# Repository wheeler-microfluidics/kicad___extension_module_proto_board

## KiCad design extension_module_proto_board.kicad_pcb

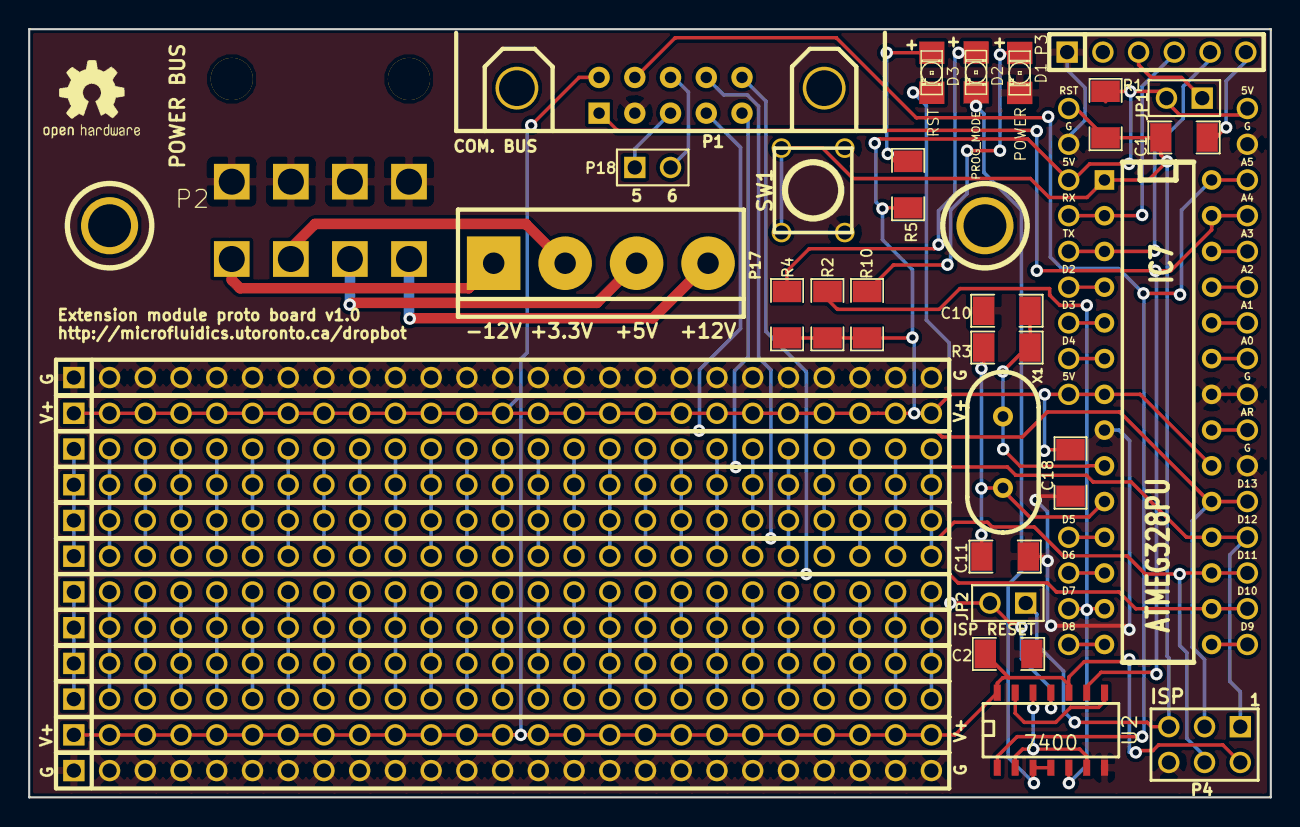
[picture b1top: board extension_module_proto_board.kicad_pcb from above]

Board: 2 copper layers, 88.3 x 54.6 mm, 41 parts (0 on the bottom side), 91 nets.

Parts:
1PIN, 1PIN#2: P***; 1pin
C1, C2, C18: 0.1uF; SM1206
C10, C11: 22pF; SM1206
D1: POWER; LED-1206
D2: PROG_MODE; LED-1206
D3: RST; LED-1206
IC7: ATMEG328PU; DIP-28
JP1: JUMPER; PIN_ARRAY_2X1
JP2: ISP RESET; PIN_ARRAY_2X1
P1: CONN_10; HE10-10C
P2: CONN_8; Molex_4x2_Mini_Fit_Jr_RA
P3: CONN_6; PIN_ARRAY-6X1
P4: CONN_6; pin_array_3x2
P5, P6, P7, P8, P9, P10, P11, P12, P13, P14, P15, P16: CONN_25; PIN_ARRAY_25X1
P17: CONN_4; bornier4
P18: CONN_2; PIN_ARRAY_2X1
R1: 10k; SM1206
R2, R4, R5, R10: 1k; SM1206
R3: 1Meg; SM1206
SW1: DPST; SW_PUSH_6mm
U1: RBBB; RBBB_shield
U2: 7400; SO14E
X1: 16MHz; HC-49V

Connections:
+3.3V PWR: P2.3, P17.2
+5V PWR: P2.2, P17.3
+5V_USB: JP1.1, P3.3
+12V PWR: P2.1, P17.4
-12V PWR: P2.4, P17.1
A0: IC7.23, U1.22
A1: IC7.24, U1.23
A2: IC7.25, U1.24
A3: IC7.26, U1.25
A4/SDA: IC7.27, P1.1, U1.26, U2.9
A5/SCL: IC7.28, P1.4, U1.27, U2.1
AREF: IC7.21, U1.20
D2: IC7.4, U1.6
D3: IC7.5, U1.7
D4: IC7.6, U1.8
D5: IC7.11, U1.10
D6: IC7.12, U1.11
D7/ISP_ENABLE: IC7.13, R2.2, U1.12, U2.5
D8: IC7.14, U1.13
D9: IC7.15, U1.14
D10: IC7.16, P1.10, U1.15
D11/MOSI: IC7.17, P1.8, P4.4, U1.16
D12/MISO: IC7.18, P1.9, P4.1, U1.17
D13/SCK: IC7.19, P1.7, P4.3, U1.18
GND: C2.1, C10.1, C11.1, C18.2, D1.2, IC7.8, IC7.22, P1.3, P2.5, P2.6, P2.7, P2.8, P3.1, P4.6, P15.1, P15.2, P15.3, P15.4, P15.5, P15.6, P15.7, P15.8, P15.9, P15.10, P15.11, P15.12, P15.13, P15.14, P15.15, P15.16, P15.17, P15.18, P15.19, P15.20, P15.21, P15.22, P15.23, P15.24, P15.25, P16.1, P16.2, P16.3, P16.4, P16.5, P16.6, P16.7, P16.8, P16.9, P16.10, P16.11, P16.12, P16.13, P16.14, P16.15, P16.16, P16.17, P16.18, P16.19, P16.20, P16.21, P16.22, P16.23, P16.24, P16.25, SW1.2, SW1.4, U1.2, U1.19, U1.21, U1.28, U2.7
unnamed: P1.6, P18.2
unnamed: C1.1, P3.6
unnamed: U2.8, U2.13
unnamed: D2.2, U2.3, U2.4
unnamed: P1.5, P18.1
unnamed: C11.2, IC7.10, R3.2, X1.1
unnamed: C10.2, IC7.9, R3.1, X1.2
unnamed: U2.2, U2.6, U2.12
unnamed: D3.2, JP2.2, U2.11
unnamed: D3.1, R5.1
unnamed: D2.1, R4.1
unnamed: D1.1, R10.1
unnamed: P7.3, P8.3, P9.3, P10.3
unnamed: P7.23, P8.23, P9.23, P10.23
unnamed: P7.14, P8.14, P9.14, P10.14
unnamed: P7.24, P8.24, P9.24, P10.24
unnamed: P7.15, P8.15, P9.15, P10.15
unnamed: P7.25, P8.25, P9.25, P10.25
unnamed: P7.16, P8.16, P9.16, P10.16
unnamed: P7.17, P8.17, P9.17, P10.17
unnamed: P7.18, P8.18, P9.18, P10.18
unnamed: P7.19, P8.19, P9.19, P10.19
unnamed: P7.1, P8.1, P9.1, P10.1
unnamed: P7.2, P8.2, P9.2, P10.2
unnamed: P7.4, P8.4, P9.4, P10.4
unnamed: P7.5, P8.5, P9.5, P10.5
unnamed: P7.6, P8.6, P9.6, P10.6
unnamed: P7.7, P8.7, P9.7, P10.7
unnamed: P7.8, P8.8, P9.8, P10.8
unnamed: P7.9, P8.9, P9.9, P10.9
unnamed: P7.10, P8.10, P9.10, P10.10
unnamed: P7.20, P8.20, P9.20, P10.20
unnamed: P7.11, P8.11, P9.11, P10.11
unnamed: P7.21, P8.21, P9.21, P10.21
unnamed: P7.12, P8.12, P9.12, P10.12
unnamed: P7.22, P8.22, P9.22, P10.22
unnamed: P7.13, P8.13, P9.13, P10.13
unnamed: P11.22, P12.22, P13.22, P14.22
unnamed: P11.13, P12.13, P13.13, P14.13
unnamed: P11.23, P12.23, P13.23, P14.23
unnamed: P11.14, P12.14, P13.14, P14.14
unnamed: P11.24, P12.24, P13.24, P14.24
unnamed: P11.15, P12.15, P13.15, P14.15
unnamed: P11.1, P12.1, P13.1, P14.1
unnamed: P11.2, P12.2, P13.2, P14.2
unnamed: P11.3, P12.3, P13.3, P14.3
unnamed: P11.4, P12.4, P13.4, P14.4
unnamed: P11.5, P12.5, P13.5, P14.5
unnamed: P11.6, P12.6, P13.6, P14.6
unnamed: P11.7, P12.7, P13.7, P14.7
unnamed: P11.8, P12.8, P13.8, P14.8
unnamed: P11.9, P12.9, P13.9, P14.9
unnamed: P11.10, P12.10, P13.10, P14.10
unnamed: P11.20, P12.20, P13.20, P14.20
unnamed: P11.11, P12.11, P13.11, P14.11
unnamed: P11.21, P12.21, P13.21, P14.21
unnamed: P11.12, P12.12, P13.12, P14.12
unnamed: P11.25, P12.25, P13.25, P14.25
unnamed: P11.16, P12.16, P13.16, P14.16
unnamed: P11.17, P12.17, P13.17, P14.17
unnamed: P11.18, P12.18, P13.18, P14.18
unnamed: P11.19, P12.19, P13.19, P14.19
RST: C1.2, IC7.1, JP2.1, P4.5, R1.1, SW1.1, SW1.3, U1.1
RX: IC7.3, P3.5, U1.5
TX: IC7.2, P3.4, U1.4
VCC: C2.2, C18.1, IC7.7, IC7.20, JP1.2, P1.2, P4.2, P5.1, P5.2, P5.3, P5.4, P5.5, P5.6, P5.7, P5.8, P5.9, P5.10, P5.11, P5.12, P5.13, P5.14, P5.15, P5.16, P5.17, P5.18, P5.19, P5.20, P5.21, P5.22, P5.23, P5.24, P5.25, P6.1, P6.2, P6.3, P6.4, P6.5, P6.6, P6.7, P6.8, P6.9, P6.10, P6.11, P6.12, P6.13, P6.14, P6.15, P6.16, P6.17, P6.18, P6.19, P6.20, P6.21, P6.22, P6.23, P6.24, P6.25, R1.2, R2.1, R4.2, R5.2, R10.2, U1.3, U1.9, U1.29, U2.10, U2.14

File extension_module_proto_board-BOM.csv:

Refs,Description,Manufacturer,Part No.,Qty
C10 C11,"Capacitor, Ceramic, 22pF, 100V, X7R, 1206","SAMSUNG ELECTRO-MECHANICS AMERICA, INC",CL31C220JCCNNNC,2
C1 C2 C18,"Capacitor, Ceramic, 0.1uf, 10%, 50V, X7R",KEMET ELECTRONICS CORPORATION,C1206C104K5RACTU,3
D1 D2 D3,"LED, Vis, Solid State, Green, 1206",KINGBRIGHT COMPANY LLC,APL3015SGC-F01,3
IC7,IC SOCKET,TE CONNECTIVITY,1-390261-9,1
JP1 JP2,"Male Headers Pins, 0.1"" spacing, 2x1",HARWIN INC,M20-9990246,2
P1,"Connector, PCB, Right Angle, 10 Position",OMRON ELECTRONICS INC,XG4A-1034,1
P2,"Mini-Fit Jr Connection header, 8POS 4.2MM R/A TIN",MOLEX INC,39301080,1
P3,"Male Headers Pins, 0.1"" spacing, 6x1, R/A",SULLINS CONNECTOR SOLUTIONS,NRPN061PARN-RC,1
P4,"Male Headers Pins, 0.1"" spacing, 3x2",HARWIN INC,M20-9980346,1
P17,CONN_4,ON SHORE TECHNOLOGY INC,OSTTC042162,1
R2 R4 R5 R10,"Resistor, Metal Film, 1k, 1%, 1/4W, 1206",STACKPOLE ELECTRONICS INC,RMCF1206FT1K00,4
R1,"Resistor, Metal Film, 10k, 1%, 1/4W, 1206",STACKPOLE ELECTRONICS INC,RMCF1206FT10K0,1
R3,"Resistor, Metal Film, 1M, 1%, 1/4W, 1206",STACKPOLE ELECTRONICS INC,RMCF1206FT1M00,1
SW1,"Switch Tactile, SPST-NO, 0.05A 12V",C&K Components,PTS645SK43 LFS,1
U2,IC Quad 2-IN NAND Gate,TEXAS INSTRUMENTS,SN74LV00ADR,1
X1,CRYSTAL 16MHZ 18PF THRU,CITIZEN FINETECH MIYOTA,HC49US-16.000MABJ-UB,1
IC8,"IC, MCU 8bit 32KB FLASH 28DIP",ATMEL,ATMEGA328P-PU,1
,,,,
Note: IC8 does not need to be placed,,,,

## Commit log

2014-05-08 Add ISP programming latch and other changes
    * change layout to make board smaller
    * replace 0603 caps with 1206 versions
    * label VCC and GND rails
    * add GND and VCC rail on either side of proto area
2014-05-28 Fix BOM and labels
2014-06-11 Fix BOM
2014-08-05 Update pos files
2016-01-20 Update .gitmodules file to point to github
2017-07-13 added appveyor.yml
2017-07-14 AppVeyor Configuration Updated
2017-07-15 AppVeyor Update: "5f61b891681557a9814440e47f9102b18ddcac59"
2017-07-17 AppVeyor Update: "ebd3acae5fa1c3216efbc6cb908b5db07f7b5100"
2017-07-17 AppVeyor Update: "f9cc8f1957b59965408d0c40c51fe03863cbf7a2"
2017-07-17 AppVeyor Update: "5d17439f61475bc23d95e0b42b680d8fb34545a9"
2017-07-18 AppVeyor Update: "ed2efe62bb2ab97aa8e77d59d2fbf27f7906765d"
2017-07-18 AppVeyor Update: "a4e909ac7a44d2708564d46a9b978b95c8367686"
2017-07-19 AppVeyor Update: "d5d159050eac48ab9123f383fe8e949476d7f60f"
2017-07-20 AppVeyor Update: "35852f667457a927c170bb71278740b12d7a8f75"
